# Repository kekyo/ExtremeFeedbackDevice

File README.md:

# Extreme feedback device (XFD) on ESP8266

* Still under construction...

## What's this?

* It's extreme feedback device (called XFD useful agile software development) running on ESP8266 (aka ESP-WROOM-02).
* I made custom schematic and artwork.
  * Use EAGLE 8
* I wrote sequencer code by C++ on ESP8266-Arduino IDE. (WIP)

## Features

* We can use signal device with 4 ports.
* For example, port 1, 2, 3 assign signal light's "Green", "Yellow" and "Red" leds. Port 4 assign buzzer.
* Signal device has to have one kind of commonly regulated voltage. I use +24V-0V based signal light.
  * Final output switcher is open-collectored transister using TOSHIBA "TD62064." https://toshiba.semicon-storage.com/info/docget.jsp?did=2229&prodName=TD62064BP1G
  * I use ARROW Electronics "AUSG-24" (In japanese): https://www.proface.co.jp/signaling/product/product_detail.php?unique_id=AUSG

## Schematic and artwork

* I'll order PCB to [Fusion PCB](https://www.seeedstudio.com/fusion_pcb.html).

## License

* Under Apache v2

## Background

* At first, I was exciting agile software development weaves. I made XFD device in 2006.
  * It was very standard formal style, using the signal light.
  * I did have no idea how to communicate easy way between PC/Server and devices. So I made with PC's printer parallel port.

* Today, we can communicate easier using a lot of procedures, USB/LAN/Wifi/Bluetooth and more. The parallel port obsoleted.
* I'm beginning to redesign for modern-style device communication. The ESP8266 totally better balanced module for IoT platform. I use ESP8266 and redesign XFD for basic boilerplate :)

## History

* first_pcb: Designed output signal with darlington transistor array. It's very simple board, contains only ESP-WROOM-02 and TrA.

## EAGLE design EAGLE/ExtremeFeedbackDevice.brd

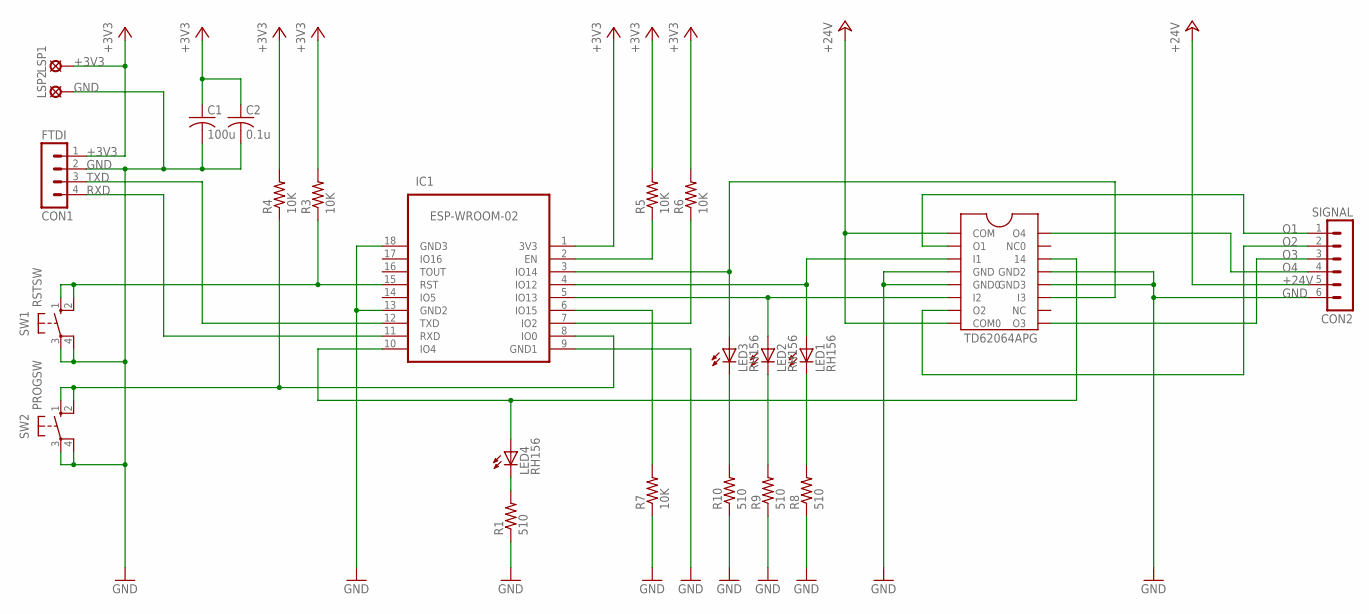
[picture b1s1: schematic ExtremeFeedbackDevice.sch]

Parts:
C1: 100u; C050-024X044
C2: 0.1u; C050-024X044
CON1: FTDI; MA04-1
CON2: SIGNAL; MA06-1
IC1: ESP-WROOM-02; FRONT-FACE
IC2: IC2; TD62064APG
LED1, LED2, LED3, LED4: RH156; LED3MM
LSP1, LSP2: LSP10
R1, R8, R9, R10: 510; 0204/7
R3, R4, R5, R6, R7: 10K; 0204/7
SW1: RSTSW; B3F-10XX
SW2: PROGSW; B3F-10XX

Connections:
+3V3: C1.1, C2.1, CON1.1, IC1.1 (3V3), LSP1.MP, R3.2, R4.2, R5.2, R6.2
+24V: CON2.5, IC2.1 (COM), IC2.8 (COM0)
GND: C1.2, C2.2, CON1.2, CON2.6, IC1.9 (GND1), IC1.13 (GND2), IC1.18 (GND3), IC2.4 (GND), IC2.5 (GND0), IC2.12 (GND3), IC2.13 (GND2), LSP2.MP, R1.1, R7.1, R8.1, R9.1, R10.1, SW1.3, SW1.4 (P1), SW2.3, SW2.4 (P1)
unnamed: IC1.8 (IO0), R4.1, SW2.1 (S), SW2.2 (S1)
unnamed: IC1.5 (IO13), IC2.6 (I2), LED2.A
unnamed: LED1.K (C), R8.2
unnamed: LED2.K (C), R9.2
unnamed: IC1.3 (IO14), IC2.11 (I3), LED3.A
unnamed: IC1.4 (IO12), IC2.3 (I1), LED1.A
unnamed: IC1.15 (RST), R3.1, SW1.1 (S), SW1.2 (S1)
unnamed: LED3.K (C), R10.2
unnamed: IC1.2 (EN), R5.1
unnamed: IC1.7 (IO2), R6.1
unnamed: IC1.6 (IO15), R7.2
unnamed: IC1.10 (IO4), IC2.14, LED4.A
unnamed: LED4.K (C), R1.2
O1: CON2.1, IC2.2 (O1)
O2: CON2.2, IC2.7 (O2)
O3: CON2.3, IC2.9 (O3)
O4: CON2.4, IC2.16 (O4)
RXD: CON1.4, IC1.11 (RXD)
TXD: CON1.3, IC1.12 (TXD)

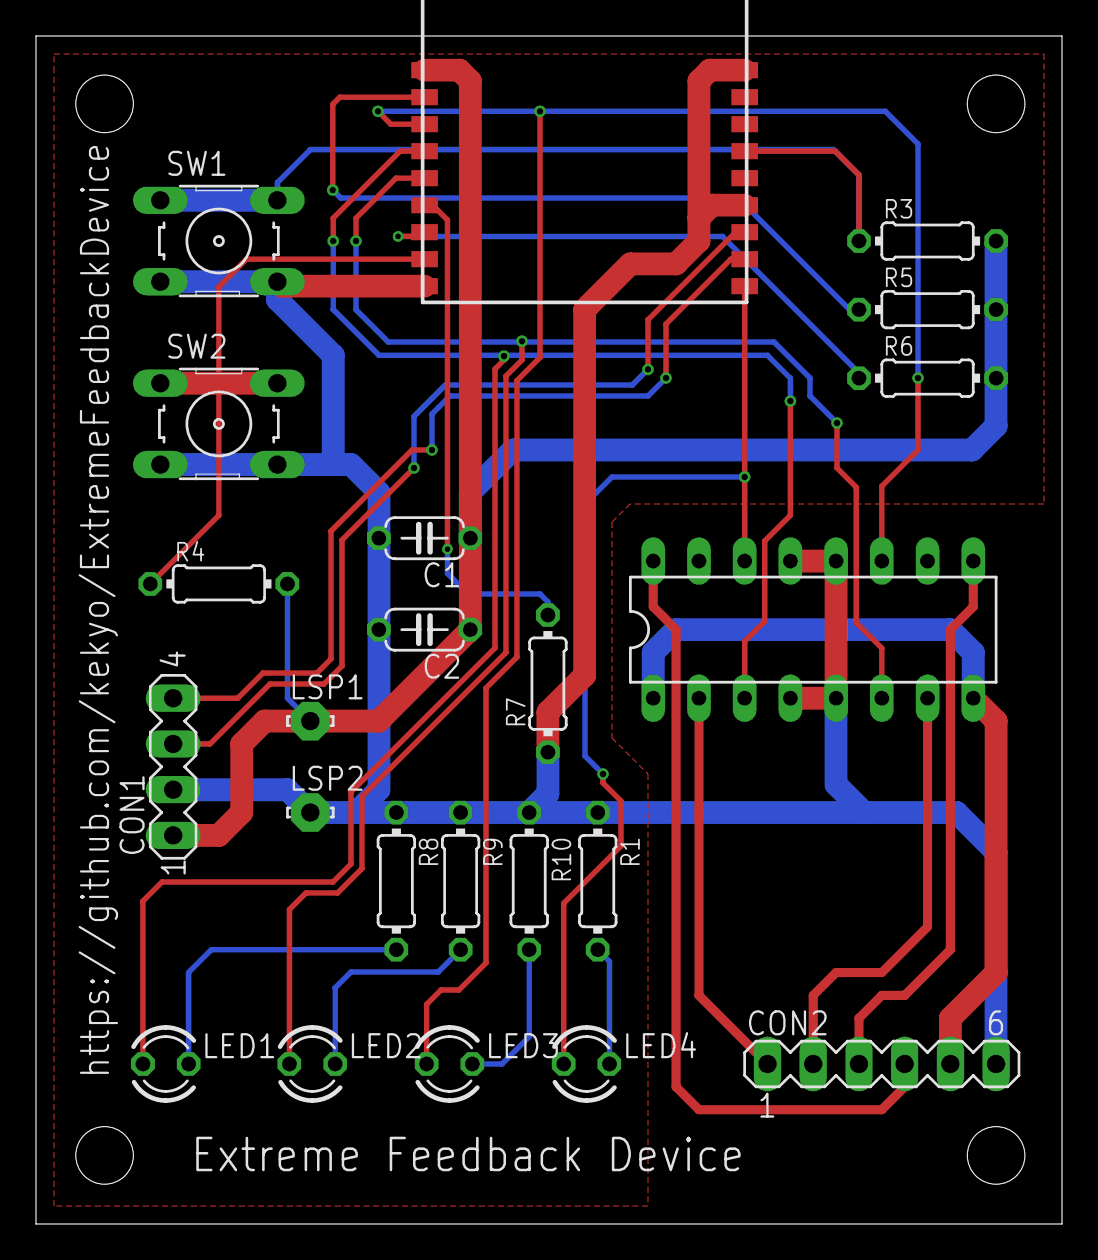
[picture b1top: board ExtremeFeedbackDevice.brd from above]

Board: 2 copper layers, 57.0 x 66.0 mm, 23 parts (0 on the bottom side), 22 nets.

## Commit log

2018-05-01 Initial commit (WIP)
2018-05-02 Finished first pcb work.
2018-05-02 Add images.
2018-05-02 Add history.
2018-05-02 Bit changed.
2018-05-17 Fixed shifted line (Invalid in DRC)
2018-05-29 Add images and update readme.
2018-06-02 Add test code.
